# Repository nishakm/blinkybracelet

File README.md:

# blinkybracelet
A bracelet with blinking LED lights

## 29 April 2017
This is more of a learning project than something that can be used and modified. Nevertheless, anyone is free to clone this project and reuse the code for driving charlieplexed LED matrices.

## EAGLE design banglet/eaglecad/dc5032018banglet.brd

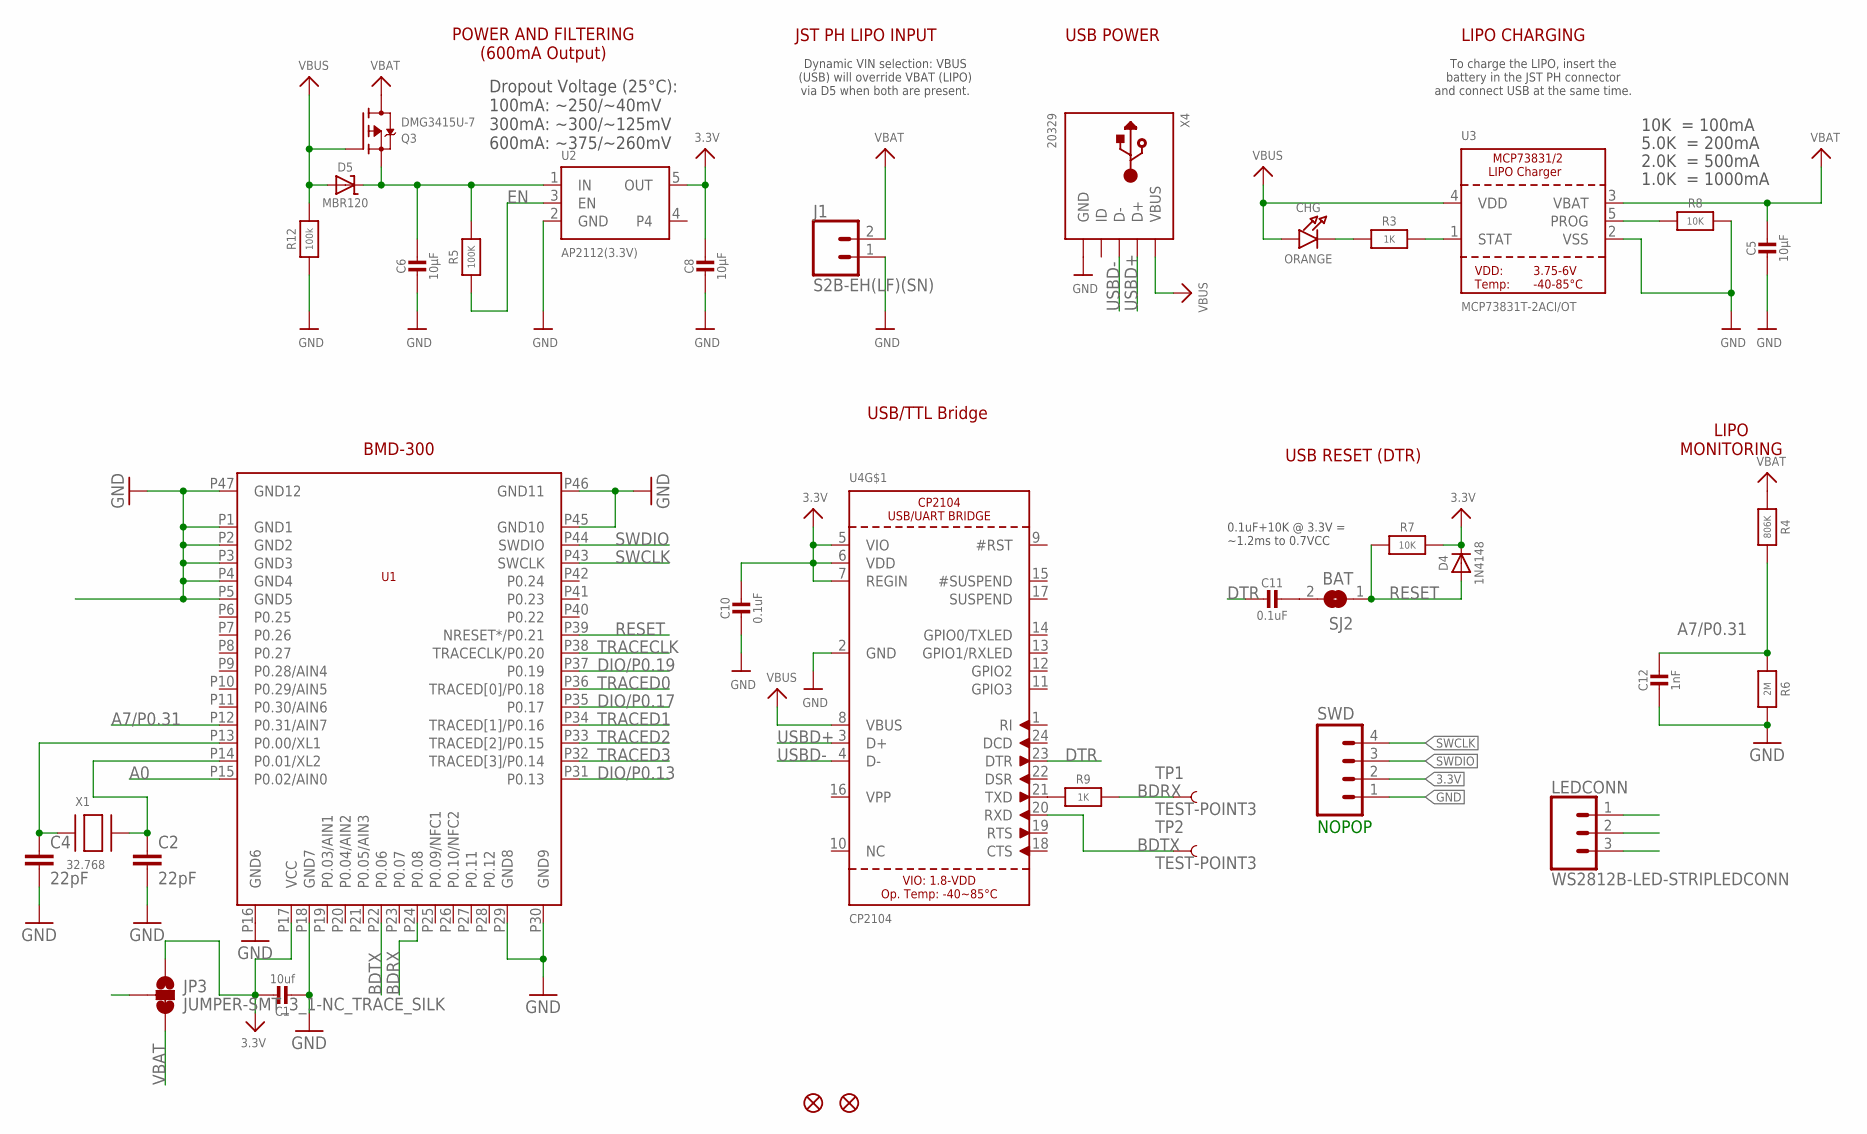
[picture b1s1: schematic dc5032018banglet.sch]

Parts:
C1: 10uf; 0805-NO
C2, C4: 22pF; 0603
C5, C6, C8: 10µF; 0805-NO
C10, C11: 0.1uF; 0603-NO
C12: 1nF; 0603-NO
CHG: ORANGE; CHIPLED_0805_NOOUTLINE
D4: 1N4148; SOD-323
D5: MBR120; SOD-123
FD1, FD2: FIDUCIALUFIDUCIAL; FIDUCIAL-MICRO
J1: S2B-EH(LF)(SN); 1X2(2.5)
JP3: JUMPER-SMT_3_1-NC_TRACE_SILK; SMT-JUMPER_3_1-NC_TRACE_SILK
LEDCONN: WS2812B-LED-STRIPLEDCONN; 1X3(2.5)
Q3: DMG3415U-7; SOT23-R
R3, R9: 1K; 0603-NO
R4: 806K; 0603-NO
R5: 100K; 0603-NO
R6: 2M; 0603-NO
R7, R8: 10K; 0603-NO
R12: 100k; 0603-NO
SJ2: BAT; SOLDERJUMPER_CLOSEDWIRE
SWD: M04LOCK; 1X04_LOCK@1
TP1, TP2: TEST-POINT3; PAD.03X.03
U1: BMD-300
U2: AP2112(3.3V); SOT23-5
U3: MCP73831T-2ACI/OT; SOT23-5
U4: CP2104; QFN24_4MM_SMSC
X1: 32.768; XTAL3215
X4: 20329; MICRO-USB5+6P-SMD-0.65-B

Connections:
3.3V: C1.1, C8.1, C10.1, D4.C, JP3.1, R7.2, SWD.2, U1.P17 (VCC), U2.5 (OUT), U4.5 (VIO), U4.6 (VDD), U4.7 (REGIN)
A0: U1.P15 (P0.02/AIN0)
A7/P0.31: C12.1, R4.2, R6.1, U1.P12 (P0.31/AIN7)
BDRX: R9.2, TP1.P$1, U1.P24 (P0.08)
BDTX: TP2.P$1, U1.P22 (P0.06), U4.20 (RXD)
DIO/P0.13: U1.P31 (P0.13)
DIO/P0.17: U1.P35 (P0.17)
DIO/P0.19: U1.P37 (P0.19)
DTR: C11.2, U4.23 (DTR)
EN: R5.1, U2.3 (EN)
GND: C1.2, C2.2, C4.2, C5.2, C6.2, C8.2, C10.2, C12.2, J1.1, R6.2, R8.2, R12.1, SWD.1, U1.P1 (GND1), U1.P2 (GND2), U1.P3 (GND3), U1.P4 (GND4), U1.P5 (GND5), U1.P16 (GND6), U1.P18 (GND7), U1.P29 (GND8), U1.P30 (GND9), U1.P45 (GND10), U1.P46 (GND11), U1.P47 (GND12), U2.2 (GND), U3.2 (VSS), U4.2 (GND), X4.5 (GND), X4.S1 (GND), X4.S2 (GND), X4.S3 (GND), X4.S4 (GND), X4.S5 (GND), X4.S6 (GND)
unnamed: C2.1, U1.P14 (P0.01/XL2), X1.P$2
unnamed: C4.1, U1.P13 (P0.00/XL1), X1.P$1
unnamed: CHG.C, R3.1
unnamed: R3.2, U3.1 (STAT)
unnamed: R8.1, U3.5 (PROG)
unnamed: R9.1, U4.21 (TXD)
unnamed: C11.1, SJ2.2
RESET: D4.A, R7.1, SJ2.1, U1.P39 (NRESET*/P0.21)
SWCLK: SWD.4, U1.P43 (SWCLK)
SWDIO: SWD.3, U1.P44 (SWDIO)
TP: U4.THERM (TP)
TRACECLK: U1.P38 (TRACECLK/P0.20)
TRACED0: U1.P36 (TRACED[0]/P0.18)
TRACED1: U1.P34 (TRACED[1]/P0.16)
TRACED2: U1.P33 (TRACED[2]/P0.15)
TRACED3: U1.P32 (TRACED[3]/P0.14)
USBD+: U4.3 (D+), X4.3 (D+)
USBD-: U4.4 (D-), X4.2 (D-)
VBAT: C5.1, J1.2, JP3.3, Q3.3 (D), R4.1, U3.3 (VBAT)
VBUS: CHG.A, D5.A, Q3.1 (G), R12.2, U3.4 (VDD), U4.8 (VBUS), X4.1 (VBUS)
VIN: C6.1, D5.C, Q3.2 (S), R5.2, U2.1 (IN)
VLED: JP3.2, LEDCONN.1

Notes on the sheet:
POWER AND FILTERING (600mA Output)
Dropout Voltage (25°C): 100mA: ~250/~40mV 300mA: ~300/~125mV 600mA: ~375/~260mV
JST PH LIPO INPUT
Dynamic VIN selection: VBUS (USB) will override VBAT (LIPO) via D5 when both are present.
USB POWER
10K = 100mA
5.0K = 200mA
2.0K = 500mA
1.0K = 1000mA
LIPO CHARGING
To charge the LIPO, insert the battery in the JST PH connector and connect USB at the same time.
LIPO MONITORING
USB RESET (DTR)
0.1uF+10K @ 3.3V = ~1.2ms to 0.7VCC
USB/TTL Bridge
NOPOP
BMD-300

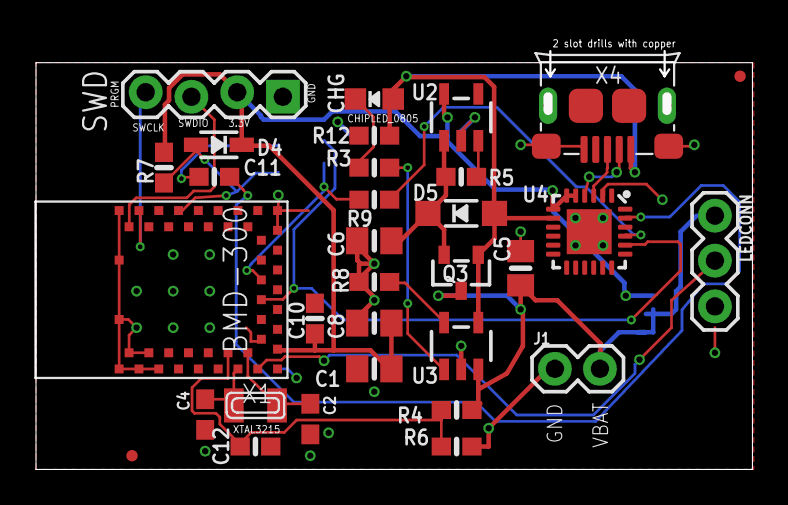
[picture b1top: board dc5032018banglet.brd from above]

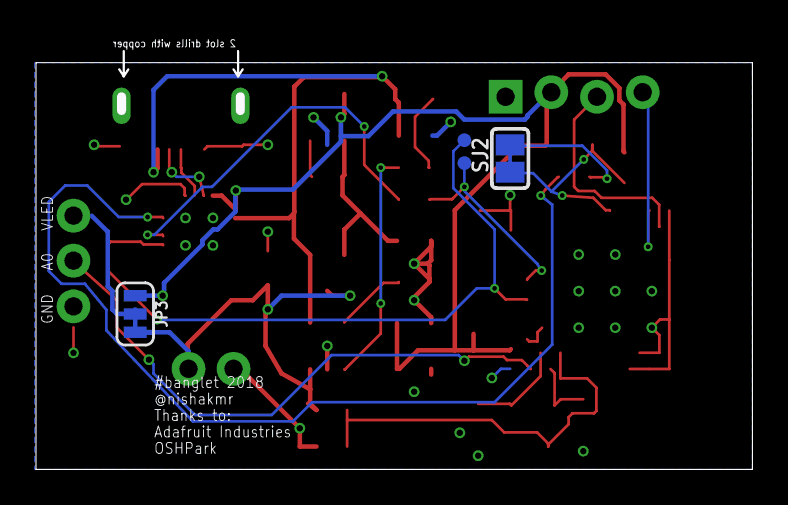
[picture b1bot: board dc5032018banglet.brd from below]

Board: 2 copper layers, 39.3 x 23.6 mm, 36 parts (4 on the bottom side), 23 nets.

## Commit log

2016-09-03 Create gh-pages branch via GitHub
2016-09-05 Modified first section
2016-09-05 Initial Arduino Uno sketch
2016-12-27 Added A unit test sketch
    - Blink one LED on pin 9
    - Blink one LED on pin 9 but connect it to pin
    10 rather than GND and drive pin 10 low
    - Blink two LEDs on pin 9 and pin 10 by pulling
    one up and pulling the other down
    - Blink a 2x2 LED matrix by pulling up and down
2016-12-31 Added unit test for charlieplexed LEDs
    The 2x2 LEDs are charlieplexed meaning that
    they are easily addressed one by one but
    cannot be turned on together
    In order to turn them on together, they
    need to be flickered. Meaning they have
    to be turned off and on quickly to make
2017-01-02 Sketch can now turn on any combination of LEDs
    This still uses a 2x2 matrix but can be expanded
    to add more.
    Right now, there is only one combination it can
    turn on and it is hardcoded.
2017-01-03 Random LEDs turn on
    Turns on a random number of LEDs
    It creates a list of LED numbers from 1 to 4
    of random length
    Also, corrected an error with the looping over
    the array of LEDs to turn on
2017-01-03 Added different loops for different number of LEDs
    From observation it seems that pinMode setup takes up
    a lot of time and increases based on how many LEDs
    are turned on. Turning on 1 LED of course is the
    fastest by far.
    There is a Serial console statement to tune the delay
    based on the number of LEDs. These should be removed
2017-01-03 Light up a group of LEDs in random combinations
    The 2x2 LED matrix will not light up a random
    number of LEDs in random positions
2017-01-13 Now driving 30 LEDs
    It requires a little work
    Some of the LEDs that I thought I was turning on don't turn on
2017-04-29 Adjust LEDs and loop timings
2017-04-29 Added a smaller set of LED rows
    This one does not have the "leakage"
    on other LEDs
2017-04-29 Added a README
    Part of a wholesale update
2017-07-30 Defcon bangle files
    Note: I have not included the Adafruit libraries because according
    to their LGPL license restrictions, I do not know for certain where their
    source files come from, whether they are version controlled, whether
    they have a release process etc. So I want to be very very careful here.
    I got the library from here: https://github.com/adafruit/Adafruit_NeoPixel
    More specifically, I used their download link here:
2018-06-07 Added WIP files for DC503 Banglet project
    - Added current state of banglet arduino sketch
    (which will probably be completely redone)
    - Added Rev 1 of the Eaglecad board and schematic files
    for the banglet BLE board
2018-06-07 Connect the unconnected; add in a junction
2018-06-08 connect uart tx/rx to bmd-300
2018-06-08 changed layout to perhaps better/easier routing. Routed.
    Opinions saught.
2018-06-09 add 2 fiducials
2018-06-10 removed NFC parts; deleted stray silk
    silk still a mess. I *think* I got all the stray labels.
2018-06-10 move X2; extend planes to dimension
2018-06-10 fix overlap of nc pads with vbat
2018-06-10 move .1uF to next to nrf
2018-06-11 Moved labels so they're clear
2018-06-11 remove some vias under bmd-300 move vias close to bmd-300 pads further away fix shorting of net with solder jumper make usb data line not quite right angle Make a0 a little less close to pads
2018-06-11 make label for LED strip a little clearer
    Move two vias away from bmd pads
2018-07-07 Removed cap and replaced JST connector with vias
    VPP on the UART is for a one time ROM programming of the UART
    which we don't need, so removing it.
    We were unable to find batteries that came with the JST female
    connectors that went with the used board mounted connector.
    Replacing it with vias to use with either board mounted breakaway
    header or something else which will fit.
2018-07-08 Simplify vbat due to through hole.
    tent vias
2018-07-08 Add banlet lib with 2.5mm part and use as J1
2018-07-11 Added new part for LED strip connection
    - Added new part to banglet library
    - Replaced vias for the LED strip with new part
    Eaglecad refuses to name the vias after the nets in the schematic
2018-07-11 connect led header in schematic and board

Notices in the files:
parts and their libraries:
microbuilder: This work is placed in the public domain, and may be freely used for commercial and non-commercial work with the following conditions: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
SparkFun-Connectors: Licensing: Creative Commons ShareAlike 4.0 International - https://creativecommons.org/licenses/by-sa/4.0
